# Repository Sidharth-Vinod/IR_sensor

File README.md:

# IR Sensor PCB Design and Schematic

## Overview  
This repository contains the complete schematic and PCB layout files for an **Infrared (IR) Sensor system** designed using KiCad. The project demonstrates a compact and efficient IR sensor circuit capable of detecting nearby objects using reflected IR light.

---

## Project Description  
The IR sensor system detects objects based on the reflection of infrared light emitted from the sensor’s LED. The design includes:  
- Schematic capture detailing all components and connections  
- PCB layout optimized for minimal noise and signal interference  
- Careful trace routing and grounding to ensure signal integrity  

---

## Applications  
This IR sensor design can be used in:  
- Proximity detection in robotics and automation  
- Obstacle detection for mobile platforms or drones  
- Simple presence detection for interactive devices  
- Line-following robots and basic object counters  

---

## Files and Content

| File Name          | Description                      |
|--------------------|----------------------------------|
| `IR_Sensor_Schematic.sch` | KiCad schematic file              |
| `IR_Sensor_PCB.kicad_pcb` | PCB layout file with component placement |

---

## Future Improvements and Scaling

- **Multi-Sensor Array:** Expand design to support multiple IR sensors for enhanced coverage and accuracy.  
- **Signal Conditioning:** Integrate amplification and filtering circuits to improve detection range and noise immunity.  
- **Wireless Integration:** Add microcontroller and wireless modules to enable remote sensing and IoT applications.  
- **Calibration & Testing:** Develop test setups for calibration to improve sensor accuracy in various environments.  
- **Miniaturization:** Optimize PCB size and component selection to fit into compact robotic platforms or wearables.  

*Thanks for visiting the project! Feel free to suggest improvements or contribute.*

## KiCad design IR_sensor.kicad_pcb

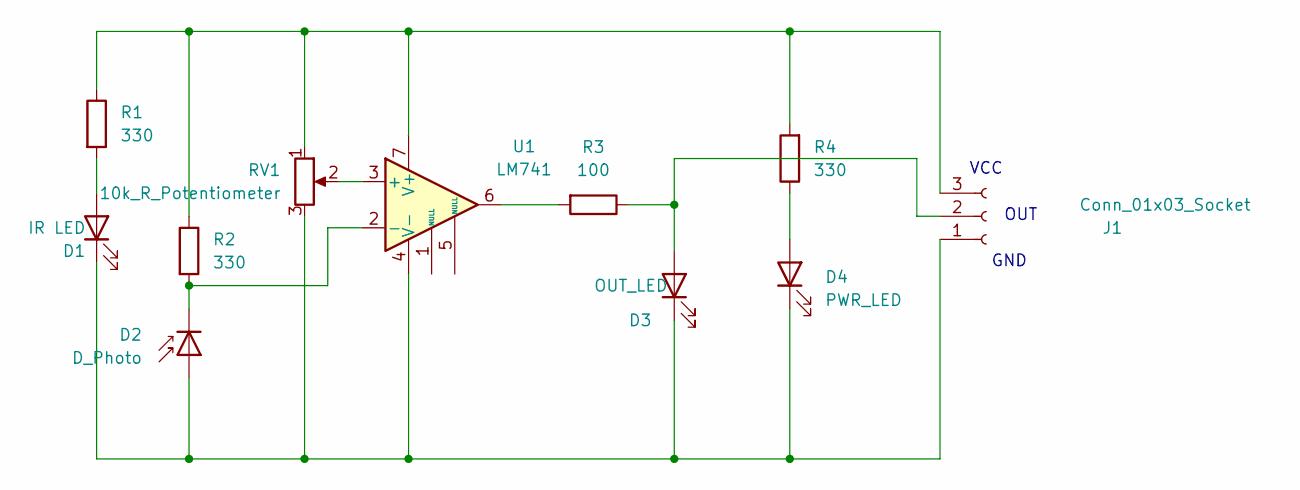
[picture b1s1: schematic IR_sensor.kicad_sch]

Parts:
D1: IR LED; LED_D5.0mm_Horizontal_O1.27mm_Z3.0mm
D2: D_Photo; LED_D5.0mm_Horizontal_O1.27mm_Z3.0mm
D3: OUT_LED; LED_0805_2012Metric_Pad1.15x1.40mm_HandSolder
D4: PWR_LED; LED_0805_2012Metric_Pad1.15x1.40mm_HandSolder
J1: Conn_01x03_Socket; PinHeader_1x03_P2.54mm_Horizontal
R1, R2, R4: 330; R_0805_2012Metric
R3: 100; R_0805_2012Metric
RV1: 10k_R_Potentiometer; Potentiometer_ACP_CA9-V10_Vertical_Hole
U1: LM741; SOIC-8_3.9x4.9mm_P1.27mm

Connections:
unnamed: D1.2 (A), R1.2
unnamed: D1.1 (K), D2.2 (A), D3.1 (K), D4.1 (K), J1.1, RV1.3, U1.4 (V-)
unnamed: D2.1 (K), R2.2, U1.2 (-)
unnamed: D3.2 (A), J1.2, R3.1
unnamed: D4.2 (A), R4.1
unnamed: J1.3, R1.1, R2.1, R4.2, RV1.1, U1.7 (V+)
unnamed: R3.2, U1.6
unnamed: RV1.2, U1.3 (+)

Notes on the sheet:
GND
VCC
OUT

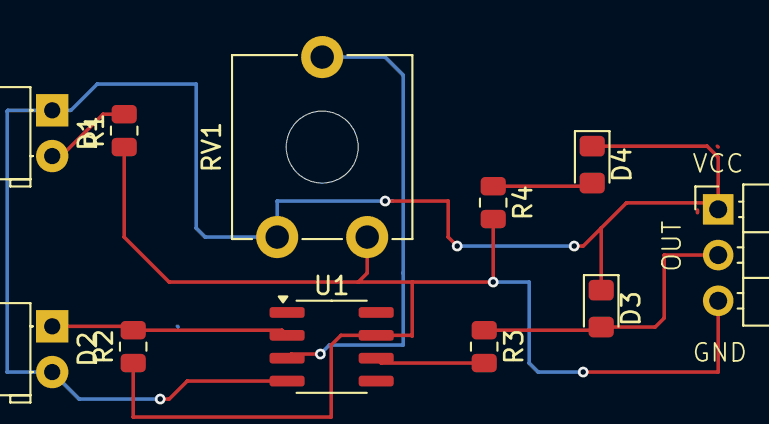
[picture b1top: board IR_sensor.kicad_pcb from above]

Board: 2 copper layers, 11 parts (0 on the bottom side), 8 nets.

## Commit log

2025-06-26 README.md
